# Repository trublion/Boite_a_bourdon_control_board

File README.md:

## Description

HW control board for motorised hurgy-gurdy. Controls a DC motor with a half-H-bridge, reads an analog audio signal envelope, dual-PCB design.

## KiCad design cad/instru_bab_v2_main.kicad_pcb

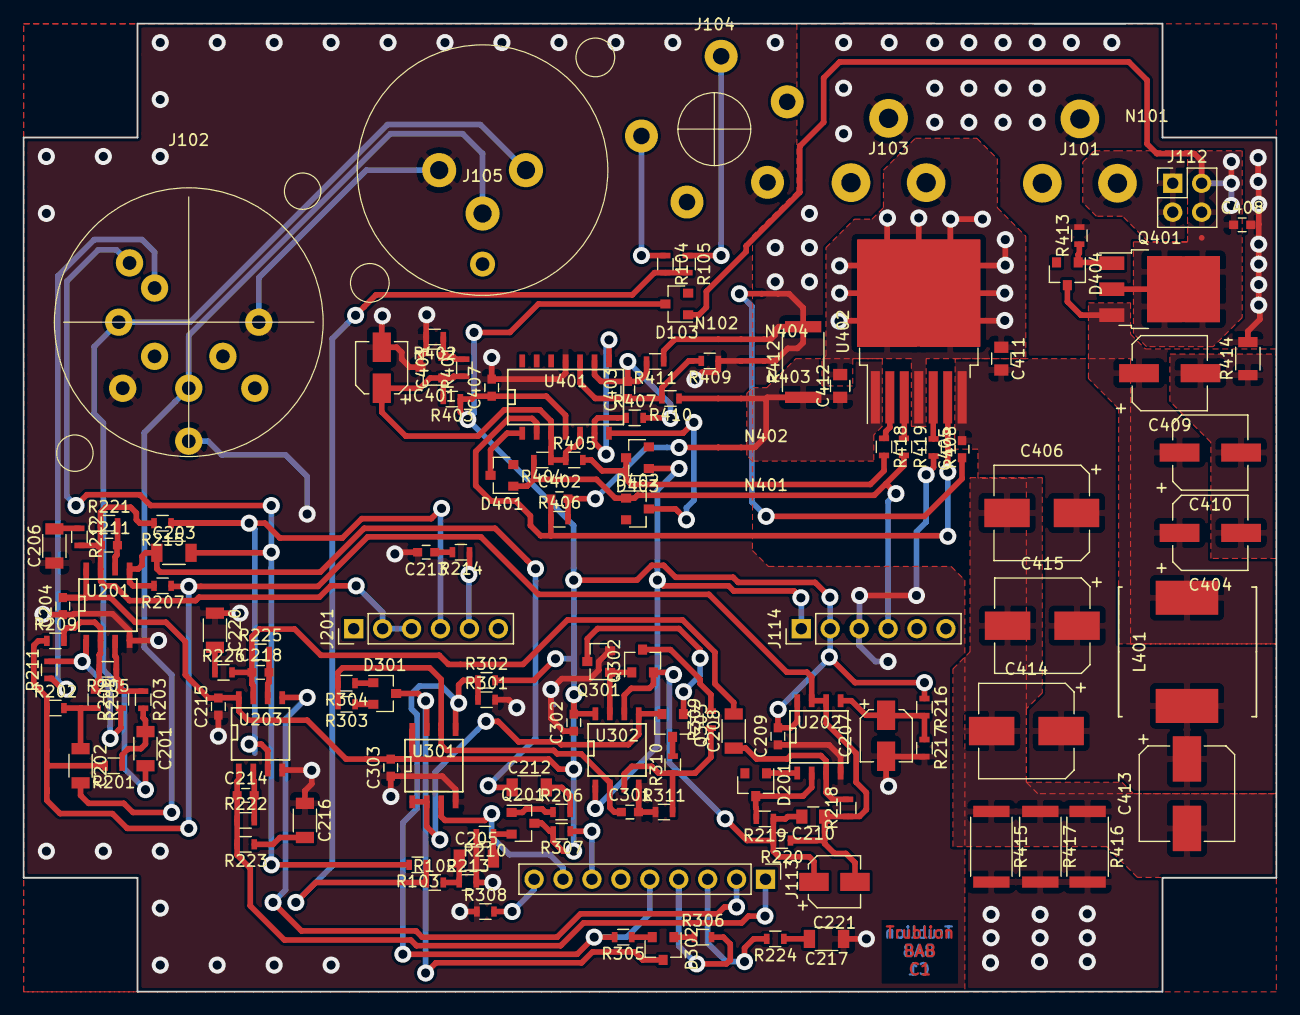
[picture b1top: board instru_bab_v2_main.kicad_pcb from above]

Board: 2 copper layers, 110.0 x 85.0 mm, 135 parts (0 on the bottom side), 86 nets.

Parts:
C201, C202, C203, C205, C206, C208, C212, C216, C217, C220: 1u; C_1206
C204, C209, C213, C215, C302, C303, C405, C407, C408: 100n; C_0603
C207, C401: 10u; CP_Elec_4x4.5
C210, C411, C412: 220n; C_0805
C211, C214, C218: 220p; C_0603
C221: 4u7; CP_Elec_4x4.5
C301, C403: 10n; C_0603
C402: 1n; C_0603
C404, C409, C410: 33u 35V; CP_Elec_6.3x5.3
C406, C413, C414, C415: 220u 35V; CP_Elec_8x10
D103, D201, D401, D402: BAS21; SOT-23
D301, D302: BAV23S; SOT-23
D403: BAT54A; SOT-23
D404: BZX84; SOT-23
IC401: TL431; SOT-23
J101, J103: L712RA; L712RA_2.5mm
J102: AUDIO_IN; NEUTRIK_NCJ9FI-V
J104: REAN_RJ3VM
J105: AUDIO_BYPASS_XLR; NC3MAAV-0
J112: CONN_02X02; Pin_Header_Straight_2x02_Pitch2.54mm
J113: CONN_01X09; Pin_Header_Straight_1x09_Pitch2.54mm
J114: CONN_LEDS_A; Pin_Header_Straight_1x06_Pitch2.54mm
J201: PAD -20dB CONNA; Pin_Header_Straight_1x06_Pitch2.54mm
L401: 100u 3A; Inductor_Coilcraft_MSS1210
N101, N102, N401, N402, N403, N404: net_tie; net_tie_0.5mm_long
Q201: Q_NPN_BEC; SOT-23
Q301: DTC114E; SOT-23
Q302, Q303: DTA114E; SOT-23
Q401: IRFR5305; TO-252-3_TabPin4
R102, R103, R219: 0; R_0603
R104, R105, R203, R204, R206, R208, R209, R211, R212, R223, R224, R226, R408, R410, R411: 1k; R_0603
R201, R202, R207, R213, R218: 1M; R_0603
R205: 22k; R_0603
R210, R214, R216, R217, R221, R222, R225, R307, R308, R401, R402, R404, R405, R406, R413, R418, R419: 10k; R_0603
R215, R220, R305, R311, R407, R409: 100k; R_0603
R301, R306: 47k; R_0603
R302: 33k; R_0603
R303: 3k3; R_0603
R304, R403: 4k7; R_0603
R309, R310: 100; R_0603
R412: 10m; R_2512
R414: 1; R_1206
R415, R416, R417: 1; R_2512
U201, U203: TL072; SOIC-8-N
U202: LM1458; SOIC-8-N
U301, U302: LM2903; SOIC-8-N
U401: LM2902; SOIC-14_N
U402: BTN8980TA; TO-263-7_TabPin8

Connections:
/AUDIO_ASYM_IN: C203.2, J102.T, R103.2
/AUDIO_ASYM_SEND: J102.TN, R211.1
/AUDIO_BYPASS: C205.1, R102.2, R213.1
/AUDIO_IN_SYM_N: C202.2, J102.3, J105.3
/AUDIO_IN_SYM_P: C201.2, J102.2, J105.2
/POT_GAIN_1: C214.1, J113.1, R222.1, R223.2, U203.1
/POT_GAIN_2: J113.2, U203.5
/POT_GAIN_3: J113.3, R224.2
/POT_MIN_1: J113.7, R307.1
/POT_MIN_2: J113.8, U301.3
/POT_MIN_3: J113.9, R308.2
/POT_THRES_1: J113.4, R306.2
/POT_THRES_2: J113.5, R301.1, R302.1, R305.2, U301.5
/motor_driver/C_COM_PWR_1: C404.2, C409.2, C410.2, R414.1
/motor_driver/C_COM_PWR_2: C406.2, C413.2, C414.2, C415.2, R415.1, R416.1, R417.1
/motor_driver/GND_MOTOR_CURR_SENSE: C412.1, N401.2, N402.2, R412.1, U402.1
/motor_driver/OUT1: C411.1, C412.2, J103.P, U402.4, U402.8
/motor_driver/PWM_IN: D403.1, J114.1, U302.1
/motor_driver/VCC_DIG: C401.1, IC401.1, R401.1, R403.2, R404.1, R405.1, U401.3, U401.5
/motor_driver/VCC_MOTOR_FILT: C405.2, C406.1, C411.2, C413.1, C414.1, C415.1, L401.1, U402.7
/motor_driver/~INH~: D401.1, D402.1, J114.4, R404.2, R419.2
/peak_detect/AUDIO_PEAK: C210.2, C221.1, Q302.2, R219.1, R220.2, U302.6
/peak_detect/VREF: C210.1, C221.2, R201.2, R202.1, R207.1, R209.1, R218.1, R220.1, U202.6, U202.7
GND: C204.1, C206.1, C207.2, C209.1, C213.2, C215.1, C216.1, C217.1, C220.1, C301.2, C302.1, C303.1, C401.2, C407.2, IC401.3, J102.1, J102.G, J102.S, J104.G, J105.1, J114.3, N102.2, Q301.2, R210.2, R213.2, R217.2, R301.2, R308.1, R311.1, R402.2, R408.2, R409.1, U201.4, U202.4, U203.4, U301.4, U302.4, U401.11
GNDPWR: C408.2, J101.S, J103.S, N102.1, N403.2, N404.2, R412.2, R413.2, R414.2, R415.2, R416.2, R417.2
unnamed: C201.1, R201.1, R203.2
unnamed: C202.1, R202.2, R204.2
unnamed: C203.1, C212.1, R207.2, U201.5
unnamed: C205.2, Q201.2, R210.1
unnamed: C206.2, R212.1
unnamed: C207.1, R216.2, R217.1, U202.5
unnamed: C208.1, R218.2, U202.3
unnamed: C208.2, C218.1, R225.1, R226.2, U203.7
unnamed: C211.1, J201.2, J201.3, R212.2, R215.2, R221.1, U201.7
unnamed: C211.2, R221.2, U201.6
unnamed: C212.2, R206.2
unnamed: C213.1, R214.2
unnamed: C214.2, R222.2, U203.2
unnamed: C216.2, R223.1
unnamed: C217.2, R224.1
unnamed: C218.2, R225.2, U203.6
unnamed: C220.2, R226.1
unnamed: C301.1, R303.2, R304.2, U301.6, U302.2
unnamed: C402.1, R406.1, U401.2, U402.6
unnamed: C402.2, N401.1, R406.2
unnamed: C403.1, R409.2, R410.2, U401.10
unnamed: C403.2, R407.2, R411.2, U401.9
unnamed: C404.1, C409.1, C410.1, D404.3, L401.2, Q401.3
unnamed: C405.1, N404.1
unnamed: D103.1, N101.2
unnamed: D201.1, U202.1
unnamed: D201.3, R219.2, U202.2
unnamed: D301.1, R304.1
unnamed: D301.2, R303.1
unnamed: D301.3, D302.3, U301.7
unnamed: D302.1, R306.1
unnamed: D302.2, R305.1
unnamed: D401.3, U401.1
unnamed: D402.3, U401.7
unnamed: D403.3, R405.2, R418.2
unnamed: D404.1, Q401.1, R413.1
unnamed: IC401.2, R401.2, R402.1
unnamed: J101.P, J112.1, J112.3
unnamed: J104.R, R105.1
unnamed: J104.T, R104.1
unnamed: J201.4, R215.1, U203.3
unnamed: J201.5, R214.1
unnamed: N402.1, R410.1
unnamed: N403.1, R411.1
unnamed: Q201.1, R206.1
unnamed: Q301.1, Q302.1, U302.7
unnamed: Q301.3, Q303.1
unnamed: Q302.3, R309.2
unnamed: Q303.2, U301.1, U301.2, U302.5
unnamed: Q303.3, R310.2
unnamed: R102.1, R103.1, R104.2, R105.2
unnamed: R203.1, R205.1, R208.2, U201.3
unnamed: R204.1, R205.2, R209.2, U201.2
unnamed: R208.1, R211.2, U201.1
unnamed: R309.1, R310.1, R311.2, U302.3
unnamed: R407.1, U401.6, U401.8
unnamed: R408.1, U402.5
unnamed: R418.1, U402.2
unnamed: R419.1, U402.3
VCC: C204.2, C209.2, C215.2, C302.2, C303.2, C407.1, D103.3, J114.2, Q201.3, R216.1, R302.2, R307.2, R403.1, U201.8, U202.8, U203.8, U301.8, U302.8, U401.4
VSS: C408.1, J112.2, J112.4, N101.1, Q401.2, Q401.4

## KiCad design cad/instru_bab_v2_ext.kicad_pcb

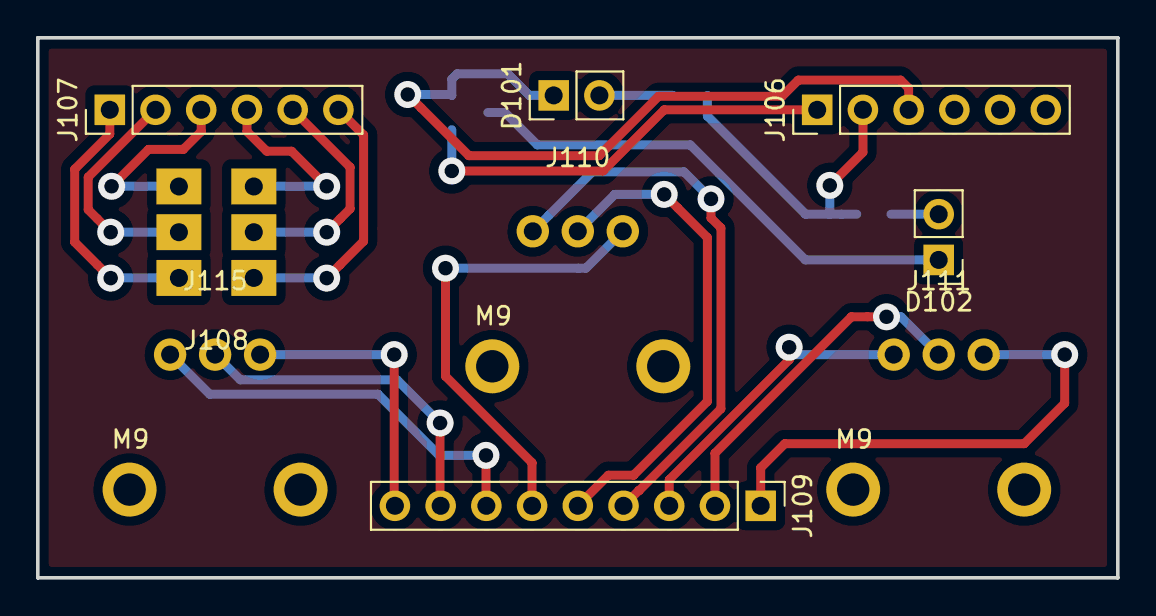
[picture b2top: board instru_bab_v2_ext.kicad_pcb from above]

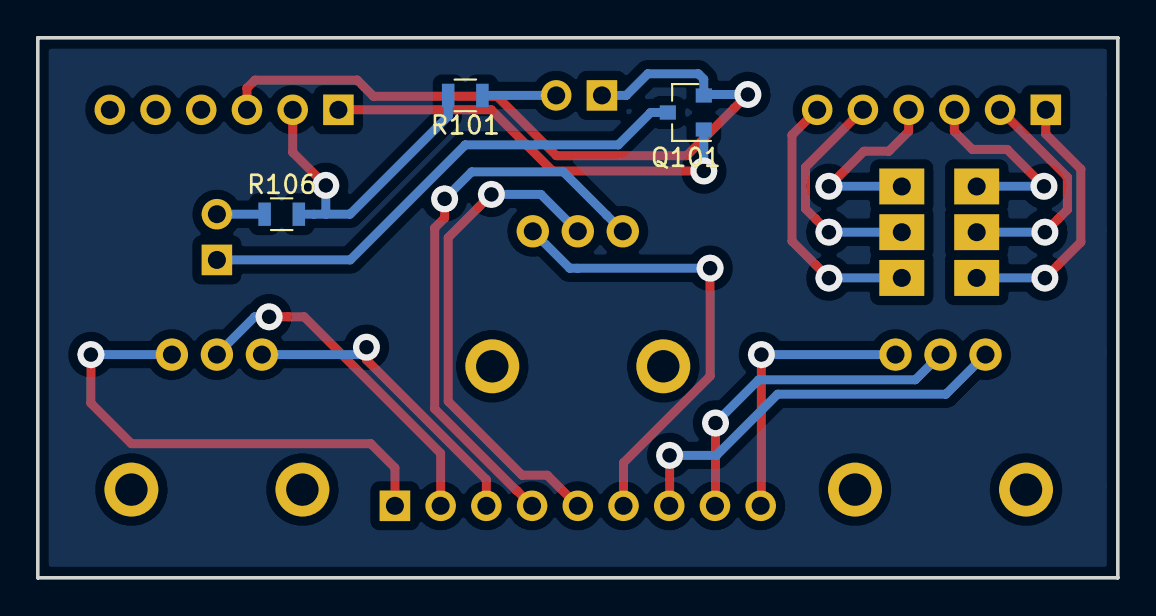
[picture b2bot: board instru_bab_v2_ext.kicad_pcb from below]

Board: 2 copper layers, 60.0 x 30.0 mm, 12 parts (3 on the bottom side), 21 nets.

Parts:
D101: LED_POWER; Pin_Header_Straight_1x02_Pitch2.54mm
D102: LED_SIGNAL; Pin_Header_Straight_1x02_Pitch2.54mm
J106: CONN_LEDS_B; Pin_Header_Straight_1x06_Pitch2.54mm
J107: CONN_SW_B; Pin_Header_Straight_1x06_Pitch2.54mm
J108: PAD CONNB; Multicomp_sub-miniature_DPDT
J109: CONN_01X09; Pin_Header_Straight_1x09_Pitch2.54mm
J110: GAIN POT; ALPS_RK09L
J111: THRESHOLD POT; ALPS_RK09L
J115: MIN POT; ALPS_RK09L
Q101: PDTA123YT; SOT-23
R101, R106: 330; R_0805

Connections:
unnamed: D101.1, J106.3, Q101.2
unnamed: D101.2, R101.1
unnamed: D102.1, Q101.3
unnamed: D102.2, R106.1
unnamed: J106.1, Q101.1
unnamed: J106.2, R101.2, R106.2
unnamed: J107.1, J108.2
unnamed: J107.2, J108.4
unnamed: J107.3, J108.6
unnamed: J107.4, J108.5
unnamed: J107.5, J108.3
unnamed: J107.6, J108.1
unnamed: J109.1, J111.1
unnamed: J109.2, J111.2
unnamed: J109.3, J111.3
unnamed: J109.4, J110.3
unnamed: J109.5, J110.2
unnamed: J109.6, J110.1
unnamed: J109.7, J115.3
unnamed: J109.8, J115.2
unnamed: J109.9, J115.1

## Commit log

2021-04-11 Initial commit.
